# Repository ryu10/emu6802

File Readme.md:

# EMU6802

[v0.6]

(日本語 | [EN](Readme_en.md))

  電脳伝説様作の [EMUZ80](https://github.com/vintagechips/emuz80) を利用した PIC16F47Q84 + MC6802 コンピュータです。

## TL;DR

 - [回路図](/img/emu6802_conv_sch.pdf)
 - [Gerber](/data/emu6802r1-gerber.zip)
 - [emu6802.X.production.hex](/data/emu6802.X.production.hex)（PIC16F47Q84 用）
 
## 機能と特徴

  - MC6802 用変換基板
  - RAM 12KB
  - Mikbug モニタ
  - Basic（フリーエリア 5.5KB）
  - PIC TU16A タイマモジュール（IRQ 割り込み可）

## 構成方法

以下の部品が必要です。

 - EMUZ80 キット（Z80 を除く）
 - PIC16F47Q84
 - EMU6802 変換基板（[Gerber](/data/emu6802r1-gerber.zip)）
 - MC6802 または互換チップ
 - DIP 40P ソケット
 - 20x1 ピンソケット x2
 - 20x1 ピンヘッダ x2（細ピンタイプ、秋月電子などで入手可）
 - （オプション）C1/C2 パスコン（0.1uF, 10uF）、J3/J4/J5 パッチベイ用ピンヘッダ（5x2, 1x1, 3x1）

上の画像では MC6802 互換の MB8870H を使用しています。

## 配線

変換基板の配線を下の回路図に示します（[PDF 版](/img/emu6802_conv_sch.pdf)）。標準でデータバス、アドレスバス、制御信号、IRQ が配線されています。

## PIC プログラム

HEX ファイル [emu6802.X.production.hex](/data/emu6802.X.production.hex) を PIC へ書き込みます（PIC18F47Q84 用です）。ソースコードは [emu6802.X](/emu6802.X/) 以下を参照してください。プロジェクトは MPLAB X IDE で開きます。

## BASIC 実行までの手順

1. EMUZ80 を組み立てます。PIC18F47Q84 を使用します。Z80 は取り付けません。
2. Z80 ソケットの外側のパターンに 20x1 ピンソケット 2 本をはんだ付けします。
3. PIC に HEX ファイル [emu6802.X.production.hex](/data/emu6802.X.production.hex) を書き込みます。なお PIC 書き込みの際は念のため 6802 または変換基板を取り外してください。
4. 変換基板を組み立てて EMUZ80 基板のピンソケットに刺します。
5. 電源投入すると EMUZ80 のシリアルポート（9600bps）から Mikbug を使用できます。
6. 'G' コマンドが参照するジャンプベクタアドレスは $2F48-$2F49です。デフォルトでジャンプベクタ $0000 が設定されているので、電源投入後すぐに 'G' キーを押すと Basic が立ち上がります。起動時の質問には下記の画面のとおり順に「12160」「80」「Y」と答えると一般的な設定が選択されます。

## 動作

EMUZ80 と同様に PIC が MPU バス信号を読み取って ROM、RAM、UART、タイマをエミュレートします。通常のハードウェアに比べてメモリ応答が遅くなるので、6802 の MR ピンを使ってシステムクロック E をストレッチしています。現状のコードでは、外部クロック入力 EXTAL に 2.3MHz を入力した場合に BASIC プログラムが最も高速に動作するようです。このとき 6802 のシステムクロック E は 387kHz 程度です。

（Ch1: EXTAL, Ch1: E, Ch3: MR）

## PIC タイマと IRQ 割り込み

PIC タイマモジュール TU16A の出力が CLC の FF 回路を経由して 6802 の IRQ に接続されます。6802 メモリ空間の \$A007 - \$A00F で TU16A の設定レジスタにアクセスできます。アドレスとレジスタの対応は下表のとおりです。

| 6802 アドレス | PIC レジスタ名  |
|--------------|---------------|
| 0xa007       | TU16ACON0     |
| 0xa008       | TU16ACON1     |
| 0xa009       | TU16AHLT      |
| 0xa00a       | TU16APS       |
| 0xa00b       | TU16ATMRH / TU16ACRH |
| 0xa00c       | TU16ATMRL / TU16ACRL |
| 0xa00d       | TU16APRH      |
| 0xa00e       | TU16APRL      |
| 0xa00f       | TU16ACLK      |
| 0xa01f       | IRQ フラグリセット   |

タイマ割り込みを応用した MC6802 時計表示プログラムが [clock.a](data/irq/clock.a) です。

また PIC コードによって動く RTC がプログラムされており、RTC の時刻データを \$B000 - \$B003 で読み書きできるようにしてあります。\$B010 への書き込みアクセスをしたタイミングで時刻がセットされます。この場合 IRQ 割り込みは不要です。これを利用した Basic 時計表示プログラムが [clock.bas](data/pictmr/clock.bas) です。

なお PIC の内部発振は誤差 2% 程度なので、実用的な RTC としては精度が不十分です。

## 課題

- PIC のメモリエミュレーションを最適化する。✅
- Altair 680 Basic を走らせる。✅
- 割り込みピンを配線する。✅
- EMUZ80 基板に載せられるアダプタボードを作る。✅
- ~~MC6802 内蔵 128 Byte RAM を有効にする。✅~~（※本リリースのデフォルト設定では無効。[リリース v0.33](https://github.com/ryu10/emu6802/tree/v0.33) を参照してください）

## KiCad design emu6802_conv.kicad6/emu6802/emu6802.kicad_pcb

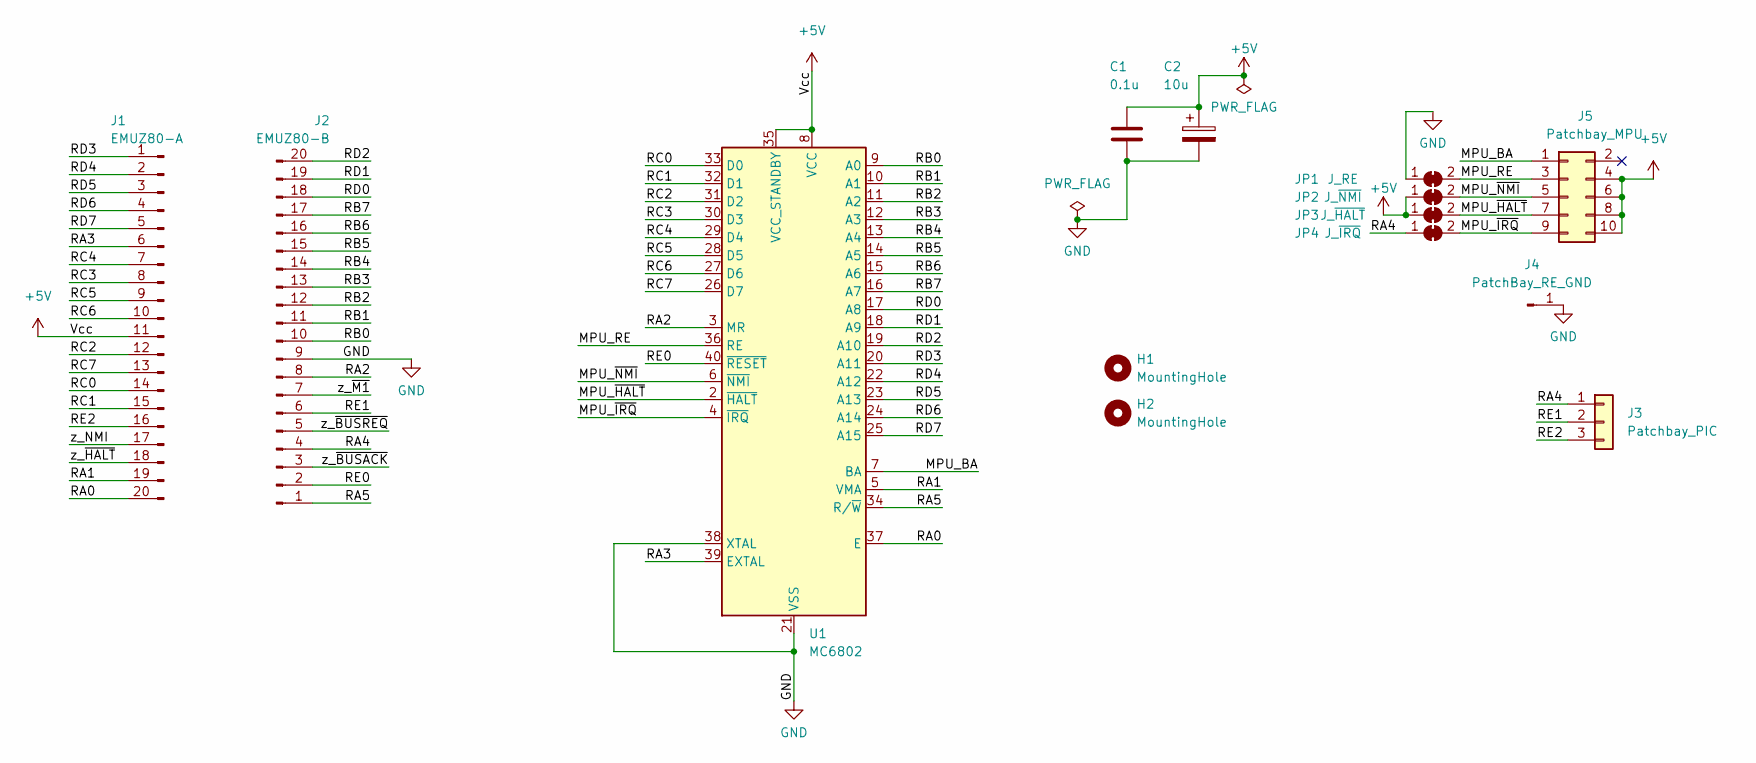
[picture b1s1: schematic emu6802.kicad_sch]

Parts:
C1: 0.1u; C_Disc_D3.0mm_W2.0mm_P2.50mm
C2: 10u; CP_Radial_D4.0mm_P2.00mm
H1, H2: MountingHole; MountingHole_3.2mm_M3
J1: EMUZ80-A; PinHeader_1x20_P2.54mm_Vertical
J2: EMUZ80-B; PinHeader_1x20_P2.54mm_Vertical
J3: Patchbay_PIC; PinHeader_1x03_P2.54mm_Vertical
J4: PatchBay_RE_GND; PinHeader_1x01_P2.54mm_Vertical
J5: Patchbay_MPU; PinHeader_2x05_P2.54mm_Vertical
JP1: J_RE; SolderJumper-2_P1.3mm_Bridged_RoundedPad1.0x1.5mm
JP2: J_~{NMI}; SolderJumper-2_P1.3mm_Bridged_RoundedPad1.0x1.5mm
JP3: J_~{HALT}; SolderJumper-2_P1.3mm_Bridged_RoundedPad1.0x1.5mm
JP4: J_~{IRQ}; SolderJumper-2_P1.3mm_Bridged_RoundedPad1.0x1.5mm
U1: MC6802; DIP-40_W15.24mm

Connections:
+5V: C1.1, C2.1, J1.11, J5.4, J5.6, J5.8, J5.10, JP2.1 (A), JP3.1 (A), U1.8 (VCC), U1.35 (VCC_STANDBY)
/MPU_BA: J5.1, U1.7 (BA)
/MPU_RE: J5.3, JP1.2 (B), U1.36 (RE)
/MPU_~HALT: J5.7, JP3.2 (B), U1.2 (~HALT)
/MPU_~IRQ: J5.9, JP4.2 (B), U1.4 (~IRQ)
/MPU_~NMI: J5.5, JP2.2 (B), U1.6 (~NMI)
/RA0: J1.20, U1.37 (E)
/RA1: J1.19, U1.5 (VMA)
/RA2: J2.8, U1.3 (MR)
/RA3: J1.6, U1.39 (EXTAL)
/RA4: J2.4, J3.1, JP4.1 (A)
/RA5: J2.1, U1.34 (R/~W)
/RB0: J2.10, U1.9 (A0)
/RB1: J2.11, U1.10 (A1)
/RB2: J2.12, U1.11 (A2)
/RB3: J2.13, U1.12 (A3)
/RB4: J2.14, U1.13 (A4)
/RB5: J2.15, U1.14 (A5)
/RB6: J2.16, U1.15 (A6)
/RB7: J2.17, U1.16 (A7)
/RC0: J1.14, U1.33 (D0)
/RC1: J1.15, U1.32 (D1)
/RC2: J1.12, U1.31 (D2)
/RC3: J1.8, U1.30 (D3)
/RC4: J1.7, U1.29 (D4)
/RC5: J1.9, U1.28 (D5)
/RC6: J1.10, U1.27 (D6)
/RC7: J1.13, U1.26 (D7)
/RD0: J2.18, U1.17 (A8)
/RD1: J2.19, U1.18 (A9)
/RD2: J2.20, U1.19 (A10)
/RD3: J1.1, U1.20 (A11)
/RD4: J1.2, U1.22 (A12)
/RD5: J1.3, U1.23 (A13)
/RD6: J1.4, U1.24 (A14)
/RD7: J1.5, U1.25 (A15)
/RE0: J2.2, U1.40 (~RESET)
/RE1: J2.6, J3.2
/RE2: J1.16, J3.3
/z_NMI: J1.17
/z_~BUSACK: J2.3
/z_~BUSREQ: J2.5
/z_~HALT: J1.18
/z_~M1: J2.7
GND: C1.2, C2.2, J2.9, J4.1, JP1.1 (A), U1.1 (VSS), U1.21 (VSS), U1.38 (XTAL)

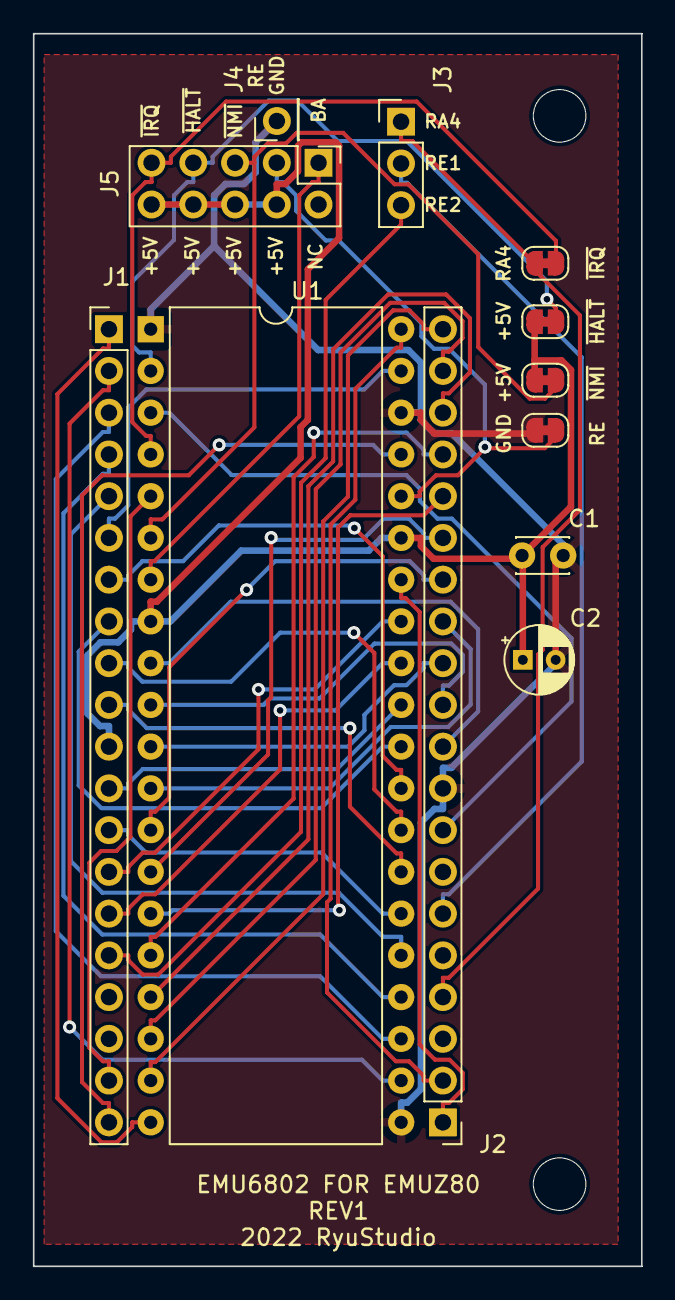
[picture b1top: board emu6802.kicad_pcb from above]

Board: 2 copper layers, 37.0 x 75.0 mm, 14 parts (0 on the bottom side), 40 nets.

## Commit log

2022-07-11 init - owc1 does not work
2022-07-14 all-wired-notwork2
2022-07-14 works with direct GPIO RA3
2022-07-14 set G2POL and G3POL now works
2022-07-16 first working code
2022-07-16 update startup mesg
2022-07-16 optimize memory access with 1) suppress CLCSELECT and 2) make MPU_DDIR = 0 (MPU read) default
2022-07-16 add schematic and readme
2022-07-16 move readme.md to top
2022-07-16 move readme.md to top (re)
2022-07-16 add schematic img to readme
2022-07-16 add release v0.21 to repo
2022-07-16 update readme with console screen
2022-07-17 update reamde
2022-07-17 separate RomRam.c
2022-07-17 allocate sparse ram locations; does not work with altair basic
2022-07-17 set mem model for altair basic; working
2022-07-17 clean data dir
2022-07-18 update romram_abasic files
2022-07-19 add readme En.
2022-07-19 udate readme_en
2022-07-19 update readmes
2022-07-19 delay changing MPU_DDIR to MPU read
2022-07-24 init branch ram128 - utilize 6802 internal sram 128b
2022-07-24 enhance ram0[] by 128b
2022-07-24 set semi-autostart Basic - just type G
2022-07-30 simplemem not working
2022-07-30 simplify mem model; working
2022-07-31 auto start copy 128B
2022-07-31 set NCO1 to exact 2MHz; no faster
2022-08-02 disable int. ram128B; working
2022-08-02 update address references in Mikbug and Basic patch; working
2022-08-02 shrink ram[] size to 8192 ; running
2022-08-02 add directive to specify rom[] ram[] addresses; working
2022-08-03 rewrite rom/ram r/w with inline assembly; working
2022-08-03 reorder write: ram-rom-uart; barely improved; working
2022-08-03 move memory access code to clc.1, written in inline assembly; working
2022-08-04 wewrite all operations with inline asm in clc.1 (and MemAccess.c)
2022-08-06 runs at 2.3MHz Extal, with single stretch for RAM access and multiple for ROM and UART
2022-08-06 remove ab.w/h/l from codes, replacing them with TBLPTRH/L; working, 385kHz
2022-08-07 add more inline assembly in clc1.c; fastest asciiart so far 19:01
2022-08-07 update readme for single isr branch
2022-08-07 update mmap
2022-08-08 replace schematic PDF
2022-08-09 update schematic
2022-08-11 add tu16A and clc6 for irq support; not working, no code yet
2022-08-13 init irq branch working
2022-08-13 in-PIC timer version
2022-09-22 update readme for pictmr, master v0.6 candidate
